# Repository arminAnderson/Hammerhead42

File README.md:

# Hammerhead42
42 key board with 24 degree angled sides with 3key support

# Current required hardware
* M2 screws
* M2 threaded inserts (https://www.amazon.com/dp/B0D477R64K?ref=ppx_yo2ov_dt_b_fed_asin_title&th=1)
* RKJXT1F42001 (https://www.digikey.com/en/products/detail/alps-alpine/RKJXT1F42001/19529127, cap here: https://www.printables.com/model/1013994-rkjxt1f42001-cap)
* 40mm cirque touchpad (https://www.mouser.com/ProductDetail/Cirque/TM040040-2024-302?qs=wd5RIQLrsJgMzmw571gvDw%3D%3D)
* 4 wires (touchpad is handwired to a breakout)
* Helios or similar (https://keeb.supply/products/0xcb-helios)
* Rubber feet
* One set of 2u stabs for right hand side (optional)

# v0.9 (current)
* Now using PCB instead of handwire

# Fixes planned for 1.0
* Right now, the case uses printed washers to help pin the case to the pcb, and rubber feet on the bottom to keep the pcb off the desk. Originally I did this to keep the thickness as minimal as possible, but I'd like to design a 2 piece case with a bottom
* Some of the mounting holes for the case on the pcb are tenths of a mm off, which probably isn't even perceptible but I want to get those perfectly aligned 
* Cases without the RKJXT1F and/or trackpad
* A way to mount the trackpad without a full case
* Full build guide
* Multiple key configurations (all 1u, for example). Currently, the non-1u keys are
  * 1.25 tab
  * 1.5 \|
  * 1.5 enter
  * 1.75 shift (left thumb)
  * 2 space (right thumb)

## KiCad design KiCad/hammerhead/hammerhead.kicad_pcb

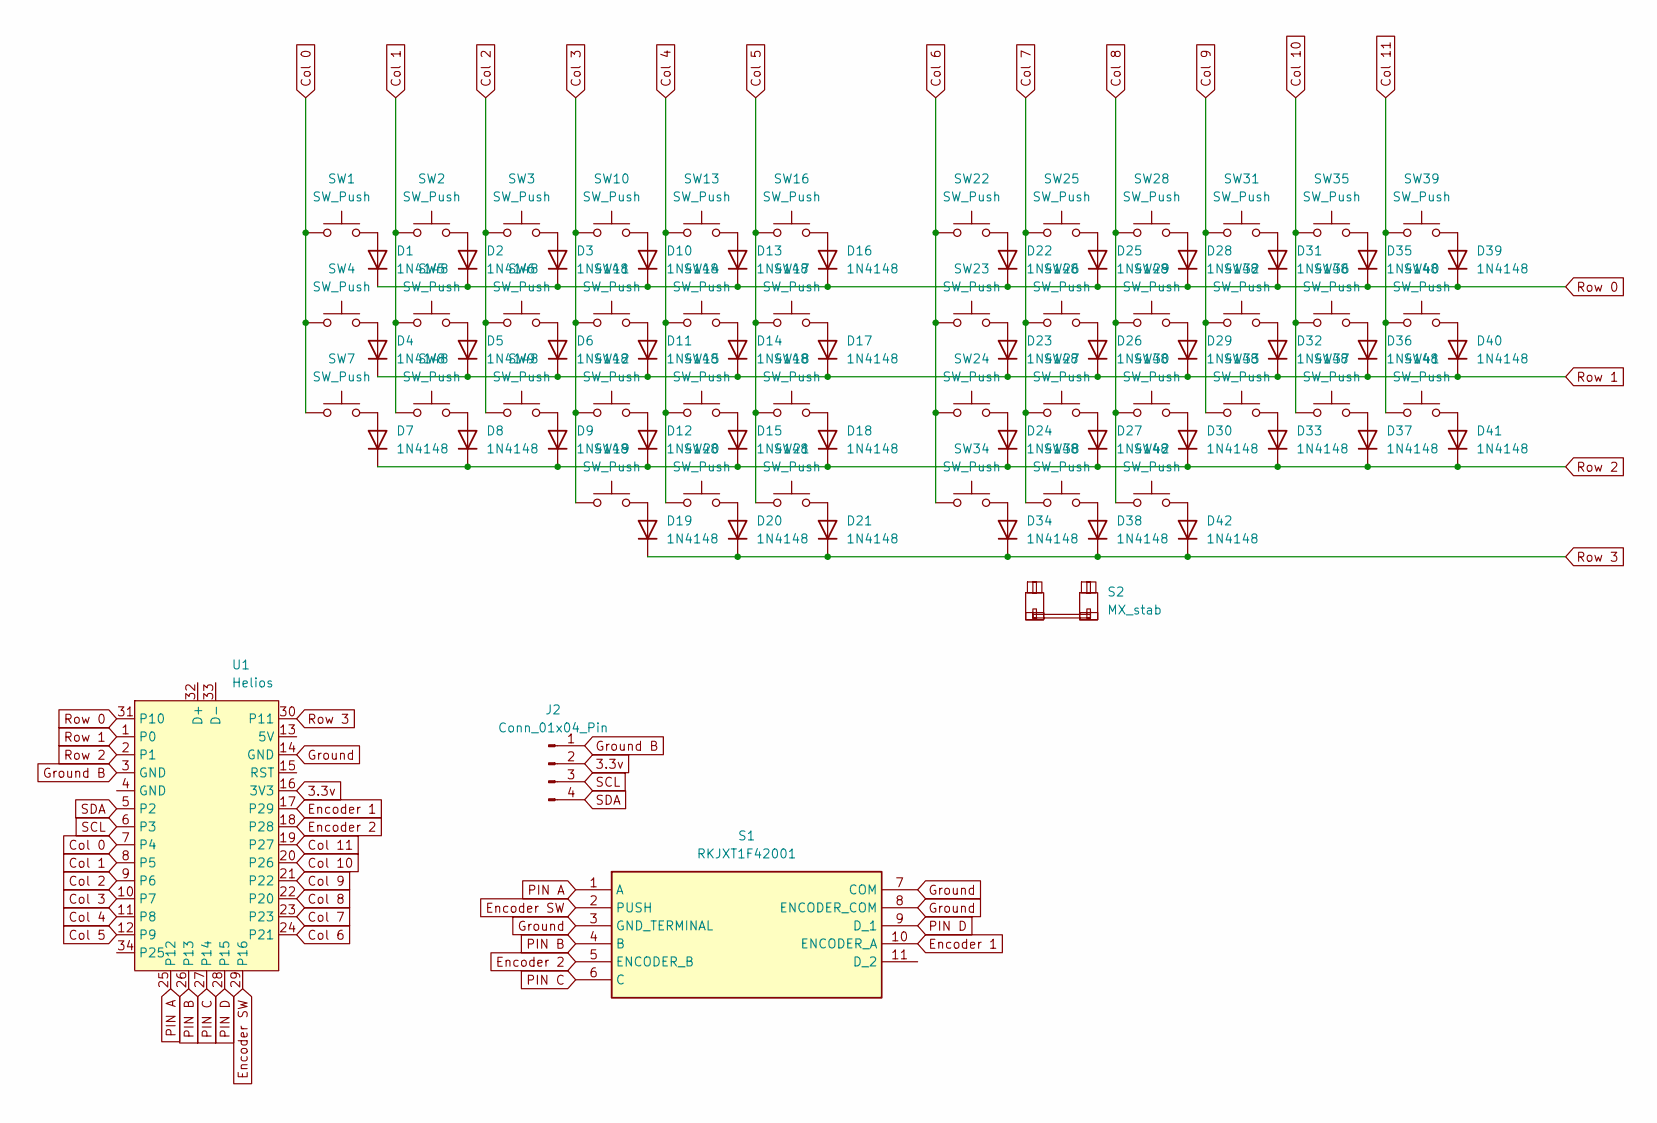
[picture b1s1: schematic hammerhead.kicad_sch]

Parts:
D1, D2, D3, D4, D5, D6, D7, D8, D9, D10, D11, D12, D13, D14, D15, D16, D17, D18, D19, D20, D21, D22, D23, D24, D25, D26, D27, D28, D29, D30, D31, D32, D33, D34, D35, D36, D37, D38, D39, D40, D41, D42: 1N4148; D_DO-35_SOD27_P7.62mm_Horizontal
J2: Conn_01x04_Pin; PinHeader_1x04_P2.54mm_Vertical
S1: RKJXT1F42001; Mouser Part Number 688-RKJXT1F42001
S2: MX_stab; STAB_MX_2u
SW1, SW2, SW3, SW5, SW6, SW7, SW8, SW9, SW10, SW11, SW12, SW13, SW14, SW15, SW16, SW17, SW18, SW19, SW21, SW22, SW23, SW24, SW25, SW26, SW27, SW28, SW29, SW30, SW31, SW32, SW33, SW34, SW35, SW36, SW37, SW41, SW42: SW_Push; SW_MX_1u
SW4: SW_Push; SW_MX_1.25u
SW20, SW38: SW_Push; SW_MX_1.75u
SW39, SW40: SW_Push; SW_MX_1.5u
U1: Helios; Helios_ACH

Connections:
3.3v: J2.2, U1.16 (3V3)
Col 0: SW1.1, SW4.1, SW7.1, U1.7 (P4)
Col 1: SW2.1, SW5.1, SW8.1, U1.8 (P5)
Col 2: SW3.1, SW6.1, SW9.1, U1.9 (P6)
Col 3: SW10.1, SW11.1, SW12.1, SW19.1, U1.10 (P7)
Col 4: SW13.1, SW14.1, SW15.1, SW20.1, U1.11 (P8)
Col 5: SW16.1, SW17.1, SW18.1, SW21.1, U1.12 (P9)
Col 6: SW22.1, SW23.1, SW24.1, SW34.1, U1.24 (P21)
Col 7: SW25.1, SW26.1, SW27.1, SW38.1, U1.23
Col 8: SW28.1, SW29.1, SW30.1, SW42.1, U1.22 (P20)
Col 9: SW31.1, SW32.1, SW33.1, U1.21 (P22)
Col 10: SW35.1, SW36.1, SW37.1, U1.20 (P26)
Col 11: SW39.1, SW40.1, SW41.1, U1.19 (P27)
Encoder 1: S1.10 (ENCODER_A), U1.17 (P29)
Encoder 2: S1.5 (ENCODER_B), U1.18 (P28)
Encoder SW: S1.2 (PUSH), U1.29 (P16)
Ground: S1.3 (GND_TERMINAL), S1.7 (COM), S1.8 (ENCODER_COM), U1.14 (GND)
Ground B: J2.1, U1.3 (GND)
unnamed: D1.2 (A), SW1.2
unnamed: D2.2 (A), SW2.2
unnamed: D3.2 (A), SW3.2
unnamed: D4.2 (A), SW4.2
unnamed: D5.2 (A), SW5.2
unnamed: D6.2 (A), SW6.2
unnamed: D7.2 (A), SW7.2
unnamed: D8.2 (A), SW8.2
unnamed: D9.2 (A), SW9.2
unnamed: D10.2 (A), SW10.2
unnamed: D11.2 (A), SW11.2
unnamed: D12.2 (A), SW12.2
unnamed: D13.2 (A), SW13.2
unnamed: D14.2 (A), SW14.2
unnamed: D15.2 (A), SW15.2
unnamed: D16.2 (A), SW16.2
unnamed: D17.2 (A), SW17.2
unnamed: D18.2 (A), SW18.2
unnamed: D19.2 (A), SW19.2
unnamed: D20.2 (A), SW20.2
unnamed: D21.2 (A), SW21.2
unnamed: D22.2 (A), SW22.2
unnamed: D23.2 (A), SW23.2
unnamed: D24.2 (A), SW24.2
unnamed: D25.2 (A), SW25.2
unnamed: D26.2 (A), SW26.2
unnamed: D27.2 (A), SW27.2
unnamed: D28.2 (A), SW28.2
unnamed: D29.2 (A), SW29.2
unnamed: D30.2 (A), SW30.2
unnamed: D31.2 (A), SW31.2
unnamed: D32.2 (A), SW32.2
unnamed: D33.2 (A), SW33.2
unnamed: D34.2 (A), SW34.2
unnamed: D35.2 (A), SW35.2
unnamed: D36.2 (A), SW36.2
unnamed: D37.2 (A), SW37.2
unnamed: D38.2 (A), SW38.2
unnamed: D39.2 (A), SW39.2
unnamed: D40.2 (A), SW40.2
unnamed: D41.2 (A), SW41.2
unnamed: D42.2 (A), SW42.2
PIN A: S1.1 (A), U1.25 (P12)
PIN B: S1.4 (B), U1.26 (P13)
PIN C: S1.6 (C), U1.27 (P14)
PIN D: S1.9 (D_1), U1.28 (P15)
Row 0: D1.1 (K), D2.1 (K), D3.1 (K), D10.1 (K), D13.1 (K), D16.1 (K), D22.1 (K), D25.1 (K), D28.1 (K), D31.1 (K), D35.1 (K), D39.1 (K), U1.31 (P10)
Row 1: D4.1 (K), D5.1 (K), D6.1 (K), D11.1 (K), D14.1 (K), D17.1 (K), D23.1 (K), D26.1 (K), D29.1 (K), D32.1 (K), D36.1 (K), D40.1 (K), U1.1 (P0)
Row 2: D7.1 (K), D8.1 (K), D9.1 (K), D12.1 (K), D15.1 (K), D18.1 (K), D24.1 (K), D27.1 (K), D30.1 (K), D33.1 (K), D37.1 (K), D41.1 (K), U1.2 (P1)
Row 3: D19.1 (K), D20.1 (K), D21.1 (K), D34.1 (K), D38.1 (K), D42.1 (K), U1.30 (P11)
SCL: J2.3, U1.6 (P3)
SDA: J2.4, U1.5 (P2)

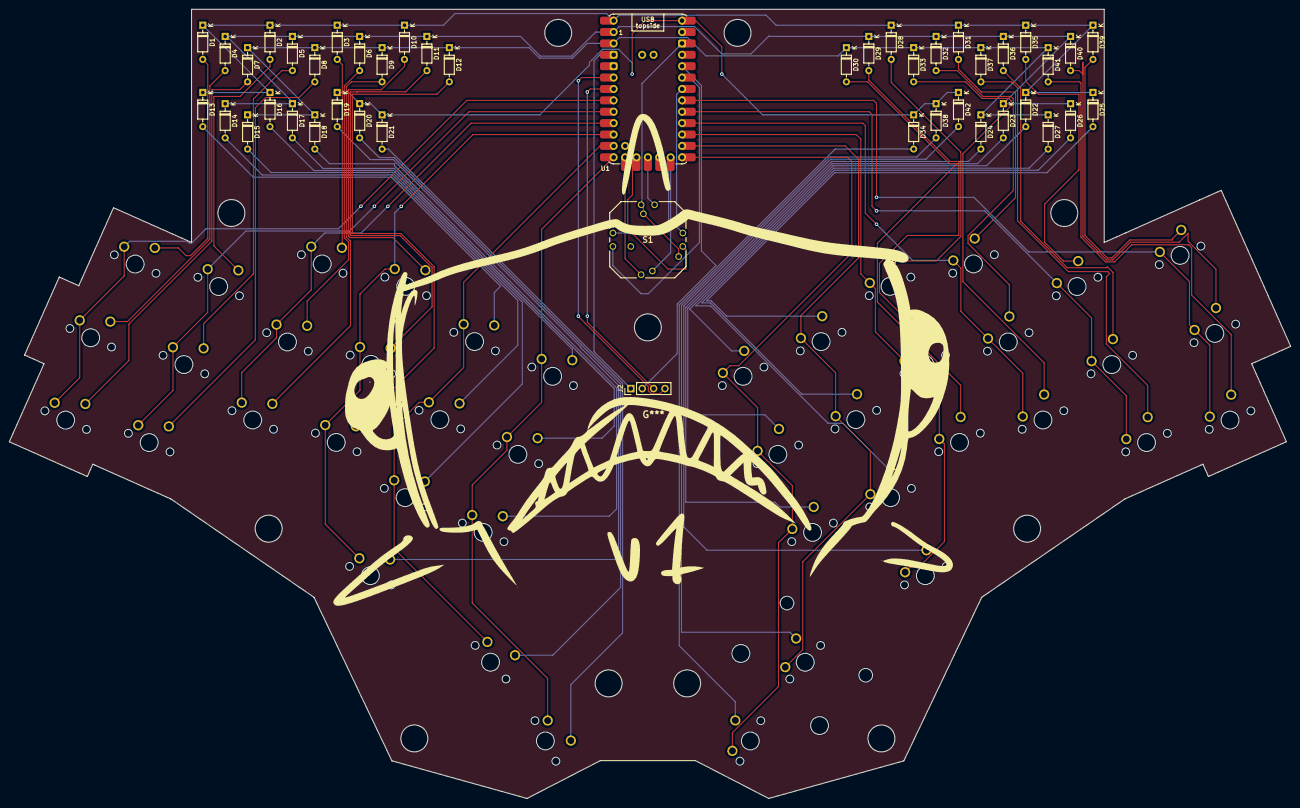
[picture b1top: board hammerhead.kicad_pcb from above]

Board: 2 copper layers, 285.8 x 176.0 mm, 88 parts (0 on the bottom side), 70 nets.

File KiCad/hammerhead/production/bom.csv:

Designator,Footprint,Quantity,Value,LCSC Part #
"D1, D10, D11, D12, D13, D14, D15, D16, D17, D18, D19, D2, D20, D21, D22, D23, D24, D25, D26, D27, D28, D29, D3, D30, D31, D32, D33, D34, D35, D36, D37, D38, D39, D4, D40, D41, D42, D5, D6, D7, D8, D9",D_DO-35_SOD27_P7.62mm_Horizontal,42,1N4148,
J2,PinHeader_1x04_P2.54mm_Vertical,1,Conn_01x04_Pin,
S1,RKJXT1F42001,1,RKJXT1F42001,
S2,STAB_MX_2u,1,MX_stab,
"SW1, SW10, SW11, SW12, SW13, SW14, SW15, SW16, SW17, SW18, SW19, SW2, SW21, SW22, SW23, SW24, SW25, SW26, SW27, SW28, SW29, SW3, SW30, SW31, SW32, SW33, SW34, SW35, SW36, SW37, SW41, SW42, SW5, SW6, SW7, SW8, SW9",SW_MX_1u,37,SW_Push,
"SW20, SW38",SW_MX_1.75u,2,SW_Push,
"SW39, SW40",SW_MX_1.5u,2,SW_Push,
SW4,SW_MX_1.25u,1,SW_Push,

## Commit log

2024-09-21 v0.9
